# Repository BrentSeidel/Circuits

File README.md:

# Circuits
A collection of my electronic circuits that may be used by other projects.  This will be
occasionally added to when I come up with something that I think may be generically useful.
Schematics specific to a particular project will generally be included with that project.

Current contents:
* 10 Conductor ribbon cable breakout board
* I/O Board providing 32 GPIO pins using 2 I2C addresses

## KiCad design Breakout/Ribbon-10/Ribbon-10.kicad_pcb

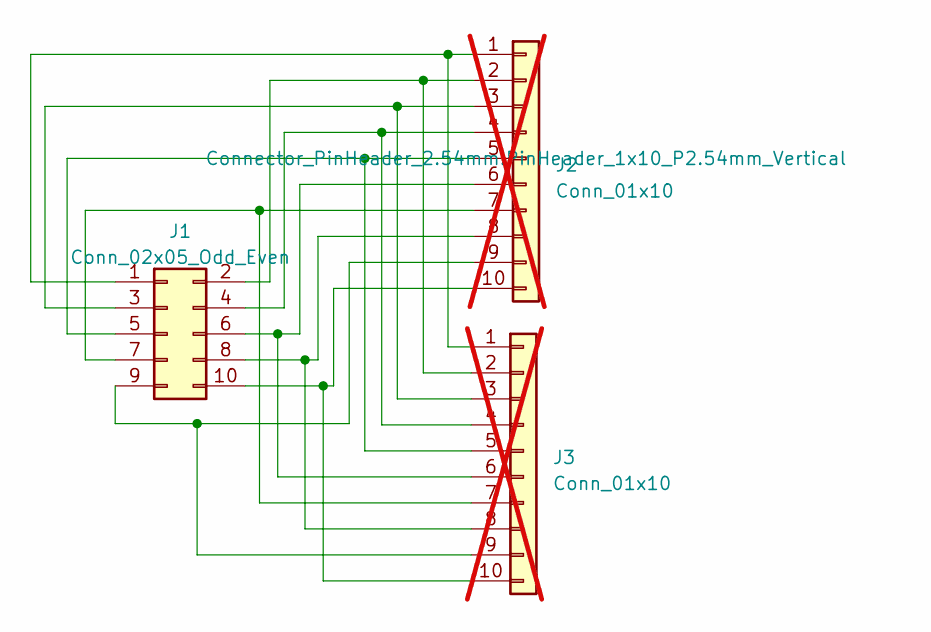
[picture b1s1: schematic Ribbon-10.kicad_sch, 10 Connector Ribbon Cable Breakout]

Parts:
J1: Conn_02x05_Odd_Even; PinHeader_2x05_P2.54mm_Horizontal
J2, J3: Conn_01x10; PinHeader_1x10_P2.54mm_Vertical; not fitted

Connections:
unnamed: J1.1, J2.1, J3.1
unnamed: J1.2, J2.2, J3.2
unnamed: J1.3, J2.3, J3.3
unnamed: J1.4, J2.4, J3.4
unnamed: J1.5, J2.5, J3.5
unnamed: J1.6, J2.6, J3.6
unnamed: J1.7, J2.7, J3.7
unnamed: J1.8, J2.8, J3.8
unnamed: J1.9, J2.9, J3.9
unnamed: J1.10, J2.10, J3.10

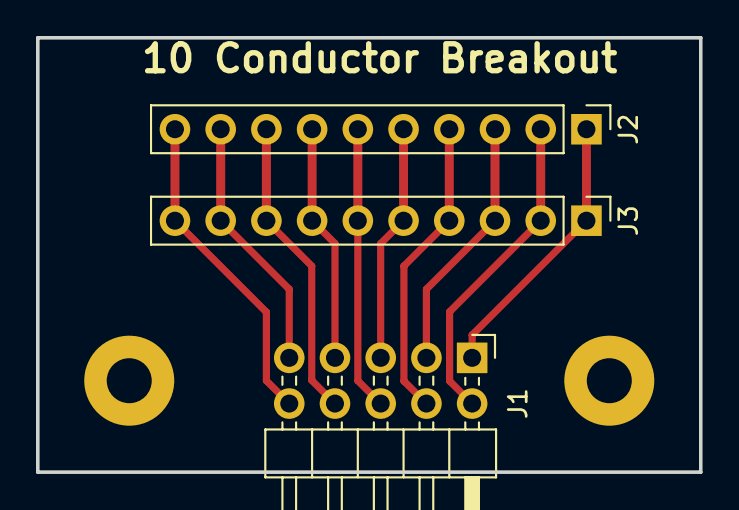
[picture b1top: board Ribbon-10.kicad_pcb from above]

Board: 2 copper layers, 36.8 x 24.1 mm, 5 parts (0 on the bottom side), 10 nets.

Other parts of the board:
REF1, REF2: MountingHole_2.5mm_Pad

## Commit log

2023-05-28 Start working on schematics and board layout for I/O board. If nothing else, the schematics will provide some documentation about how things should be wired up. Note that this may not be consistent w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
2023-06-13 Update schematic and PCB to use resistor symbols instead of jumpers.
2023-06-19 Update PCB to use SMD resistors and rectangular connectors. This lets the PCB shrink some more and it may be easier to crimp rectangular connectors onto ribbon cable than to solder a bunch of D-9 con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
2023-07-09 Update schematic to add resisters on inputs as well. Submitted PCB for production. Once PCBs are received, assembled, tested, and working, I'll update documentation.
2023-07-24 Fix schematic error and re-layout board. Start a tray to hold board.
2023-07-26 More updates to I/O board PCB layout.
2023-07-28 Updates to PCB layout to add silkscreen blocks for notes.
2023-08-08 Add 10 conductor ribbon cable breakout board.
2023-08-08 Updates to 10 conductor ribbon cable breakout board.
2023-08-09 Enlarge breakout board traces and add silkscreened title.
2023-08-11 Move I/O Board schematics to proper directory.
2023-08-11 Update README to add I/O board. Change trace width on breakout board
2023-08-14 Add documentation for I/O Board
